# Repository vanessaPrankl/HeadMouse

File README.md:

# HeadMouse
 
This project provides hardware, enclosure and software for the head-motion based computermouse HeadMouse.

## Hardware
A BOM and PCB-files are provided in the hardware folder. A 600mAh LiPo-battery has been used for the prototyping, the battery only lasts for 3.5h in this case which is mainly caused by the high power consumption of the ESP32-S3-WROOM buetooth module. 

## Software
The following external libraries are utilized:
| Library | Provider | Licence |  
|------|----------|---------|
| [BleMouse](https://github.com/T-vK/ESP32-BLE-Mouse) | [T-vK](https://github.com/T-vK) | MIT License |
| [AdafruitBNO055](https://github.com/adafruit/Adafruit_BNO055) | [Adafruit](https://github.com/adafruit) | MIT License |
| [ESP32_TimerInterrupt](https://github.com/khoih-prog/ESP32TimerInterrupt) | [khoih-prog](https://github.com/khoih-prog) | MIT License|

Additionally, a HeadMouse library including major HeadMouse functions is provided. 

The hardware pins are configured in the hm_board_config_v1_0.hpp file of the headmouse library.
The default preferences are set in default_preferences.hpp (include folder of project).

## Enclosure
The enclosure consists of 2 3D-printed parts, 2 screws and according nuts for assembly and a sticky clip for mounting the deivce on the user's head.

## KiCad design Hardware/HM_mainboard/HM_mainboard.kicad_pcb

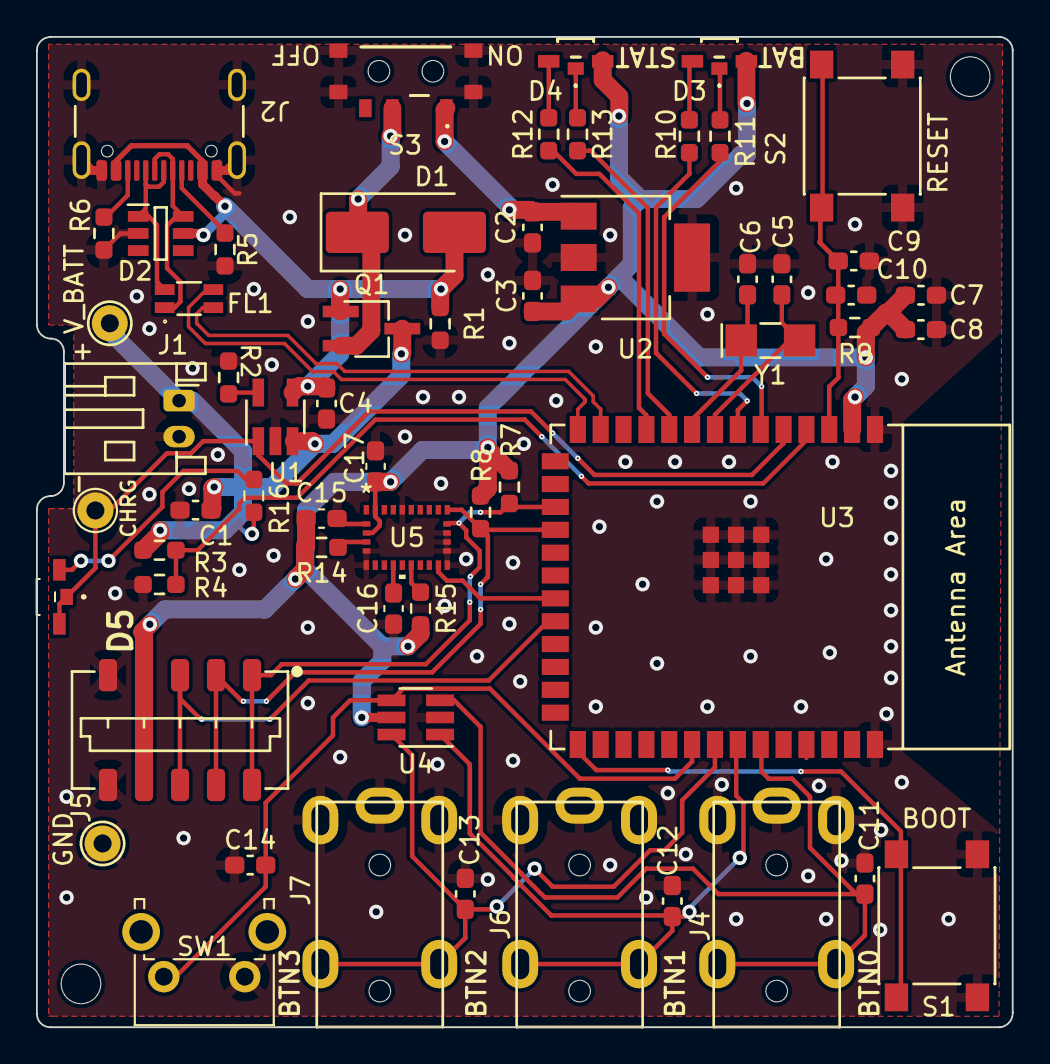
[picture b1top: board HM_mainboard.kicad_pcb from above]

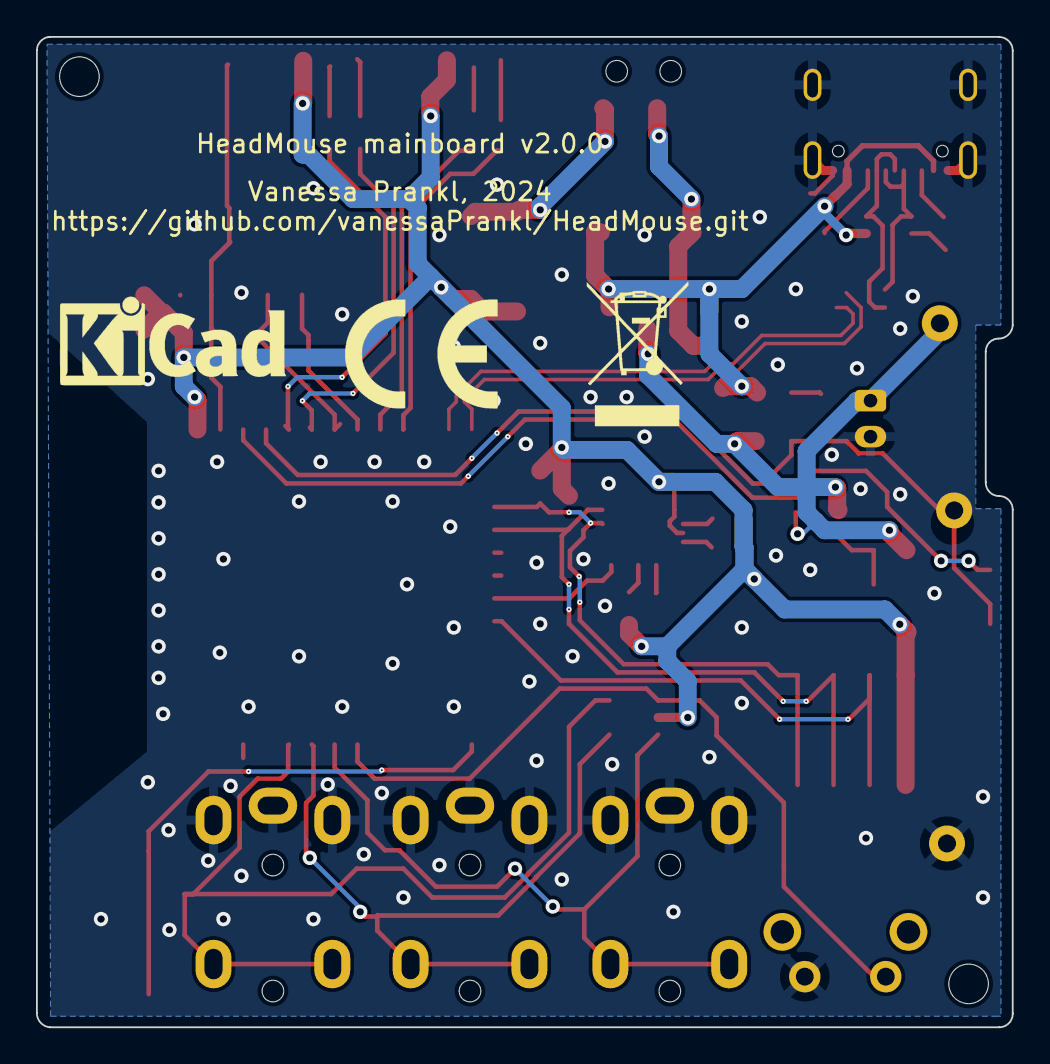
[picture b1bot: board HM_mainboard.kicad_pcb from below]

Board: 2 copper layers, 54.2 x 55.0 mm, 65 parts (3 on the bottom side), 39 nets.

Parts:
C1, C4: 4.7uF; C_0603_1608Metric_Pad1.08x0.95mm_HandSolder
C2, C3, C10, C16: 1.0uF; C_0603_1608Metric_Pad1.08x0.95mm_HandSolder
C5, C6: 15pF-1%; C_0603_1608Metric_Pad1.08x0.95mm_HandSolder
C7: 22uF; C_0603_1608Metric_Pad1.08x0.95mm_HandSolder
C8, C9, C11, C12, C13, C14, C15, C17: 100nF; C_0603_1608Metric_Pad1.08x0.95mm_HandSolder
D1: 10BQ015; D_SMB_Handsoldering
D2: WE-TVS-824015; SOT95P280X145-6N
D3, D4, D5: 155124RV73200
FL1: WE-CNSW 744232090; WE-CNSW-SMD
H1, H2: MountingHole; MountingHole_2.2mm_M2_ISO7380
J1: JST PH2P ST90; JST_PH_S2B-PH-K_1x02_P2.00mm_Horizontal
J2: USB4105-GF-A; USB_C_Receptacle_GCT_USB4105-xx-A_16P_TopMnt_Horizontal
J4, J6, J7: 54-00174
J5: 009159005551906
LOGO1: Logo_HM; LOGO_HM_V2.0.0
LOGO2: Logo_KiCAD; KiCad-Logo_5mm_SilkScreen
LOGO3: Logo_CE; CE-Logo_8.5x6mm_SilkScreen
LOGO4: Logo_WEEE; WEEE-Logo_5.6x8mm_SilkScreen
Q1: PMOS AS3401; TSOT-23_HandSoldering
R1, R9, R14, R15: 10k; R_0603_1608Metric_Pad0.98x0.95mm_HandSolder
R2: 2k; R_0603_1608Metric_Pad0.98x0.95mm_HandSolder
R3, R4: 100k; R_0603_1608Metric_Pad0.98x0.95mm_HandSolder
R5, R6: 5k1; R_0603_1608Metric_Pad0.98x0.95mm_HandSolder
R7: 4k7; R_0603_1608Metric_Pad0.98x0.95mm_HandSolder
R8: 1k8; R_0603_1608Metric_Pad0.98x0.95mm_HandSolder
R10, R11, R12, R13: 120; R_0603_1608Metric_Pad0.98x0.95mm_HandSolder
R16: 1k; R_0603_1608Metric_Pad0.98x0.95mm_HandSolder
S1, S2: SW_Push; SW_Push_1P1T_NO_6x6mm_H9.5mm
S3: 450404015514
SW1: SKHHLQA010; SW_Tactile_SPST_Angled_PTS645Vx58-2LFS
TP2, TP4, TP5: TestPoint_Probe; TestPoint_THTPad_D2.0mm_Drill1.0mm
U1: MCP73831-2; SOT-23-5_HandSoldering
U2: TC1262-33; SOT-223-3_TabPin2
U3: ESP32-S3-WROOM-1
U4: WE-TVS-824015043; SOT-23-6_Handsoldering
U5: BNO055; QFN_BNO055_BOS
Y1: 32.768 kHz; Crystal_SMD_MicroCrystal_CC7V-T1A-2Pin_3.2x1.5mm_HandSolder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

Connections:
3.3V: C3.1, C7.2, C8.2, C15.1, C17.1, D3.2 (A), D4.2 (A), J5.4, R7.2, R8.2, R9.2, R14.2, R15.2, U2.3 (VO), U3.2 (3V3), U4.5 (VBUS), U5.3 (VDD), U5.28 (VDDIO)
/BAT_CHRG_STATUS: D5.1 (K1), D5.3 (K2), TP4.1, U1.1 (STAT), U3.5 (GPIO5/TOUCH5/ADC1_CH4)
/BNO55_INT: U3.21 (GPIO13/TOUCH13/ADC2_CH2/FSPIQ/FSPIIO7/S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), U5.14 (INT)
/BTN_1: C11.1, J4.4, J4.5, U3.35 (MTMS/GPIO42), U4.3 (I/O2)
/BTN_2: C12.1, J6.4, J6.5, U3.34 (MTDI/GPIO41/CLK_OUT1), U4.1 (I/O1)
/BTN_3: C13.1, J7.4, J7.5, U3.33 (MTDO/GPIO40/CLK_OUT2), U4.6 (I/O4)
/BTN_4: C14.1, SW1.2, U3.32 (MTCK/GPIO39/CLK_OUT3/SUBSPICS1), U4.4 (I/O3)
/Battery_and_Power_Managment/V_IN: C2.1, S3.1, U2.1 (VI)
/Battery_and_Power_Managment/V_PWR_SWITCH: D1.1 (C), Q1.2 (S), S3.2
/I2C_SCL: J5.1, R7.1, U3.17 (GPIO9/TOUCH9/ADC1_CH8/FSPIHD/SUBSPIHD), U5.19 (COM1)
/I2C_SDA: J5.2, R8.1, U3.18 (GPIO10/TOUCH10/ADC1_CH9/FSPICS0/FSPIIO4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), U5.20 (COM0)
/LED_BAT_G: R10.1, U3.7 (GPIO7/TOUCH7/ADC1_CH6)
/LED_BAT_R: R11.1, U3.6 (GPIO6/TOUCH6/ADC1_CH5)
/LED_STAT_G: R12.1, U3.11 (GPIO18/U1RXD/ADC2_CH7/CLK_OUT3)
/LED_STAT_R: R13.1, U3.10 (GPIO17/U1TXD/ADC2_CH6)
/MPRLS_INT: J5.3, U3.22 (GPIO14/TOUCH14/ADC2_CH3/FSPIWP/FSPIDQS/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)
/Microcontroller - ESP32-S3-WROOM/BOOT: S1.2, U3.27 (GPIO0/BOOT)
/Microcontroller - ESP32-S3-WROOM/EN: C9.2, C10.2, R9.1, S2.2, U3.3 (EN)
/Microcontroller - ESP32-S3-WROOM/USB_C_D+: FL1.3, U3.14 (GPIO20/U1CTS/ADC2_CH9/CLK_OUT1/USB_D+)
/Microcontroller - ESP32-S3-WROOM/USB_C_D-: FL1.2, U3.13 (GPIO19/U1RTS/ADC2_CH8/CLK_OUT2/USB_D-)
/V_BAT_MEASURE: R3.1, R4.2, U3.4 (GPIO4/TOUCH4/ADC1_CH3)
GND: C1.2, C2.2, C3.2, C4.2, C5.1, C6.1, C7.1, C8.1, C9.1, C10.1, C11.2, C12.2, C13.2, C14.2, C15.2, C16.1, C17.2, D2.2 (GND), J1.2, J2.A1 (GND), J2.A12 (GND), J2.B1 (GND), J2.B12 (GND), J2.S1 (SHIELD), J4.1, J4.2, J4.3, J5.5, J6.1, J6.2, J6.3, J7.1, J7.2, J7.3, R1.1, R2.1, R4.1, R5.1, R6.1, S1.1, S2.1, S3.MP1, S3.MP2, S3.MP3, S3.MP4, SW1.1, TP5.1, U1.2 (V_{SS}), U2.2 (GND), U3.1 (GND), U3.40 (GND), U3.41 (GND), U4.2 (GND), U5.2 (GND), U5.5 (PS1), U5.6 (PS0), U5.15 (Pin15), U5.16 (Pin16), U5.17 (COM3), U5.18 (COM2), U5.25 (GNDIO)
unnamed: D2.1 (I/O), FL1.4, J2.A6 (D+), J2.B6 (D+)
unnamed: D2.6 (I/O), FL1.1, J2.A7 (D-), J2.B7 (D-)
unnamed: D3.1 (K1), R11.2
unnamed: D3.3 (K2), R10.2
unnamed: D4.1 (K1), R13.2
unnamed: D4.3 (K2), R12.2
unnamed: D5.2 (A), R16.1
unnamed: J2.A5 (CC1), R5.2
unnamed: J2.B5 (CC2), R6.2
unnamed: R2.2, U1.5 (PROG)
unnamed: C5.2, U3.8 (GPIO15/U0RTS/ADC2_CH4/XTAL_32K_P), Y1.2
unnamed: C6.2, U3.9 (GPIO16/U0CTS/ADC2_CH5/XTAL_32K_N), Y1.1
unnamed: C16.2, U5.9 (CAP)
unnamed: R14.1, U5.4 (NBOOT_LOAD_PIN)
unnamed: R15.1, U5.11 (NRESET)
V_BATT: C1.1, J1.1, Q1.3 (D), R3.2, R16.2, TP2.1, U1.3 (V_{BAT})
V_USB: C4.1, D1.2 (A), D2.5 (VDD), J2.A4 (VBUS), J2.A9 (VBUS), J2.B4 (VBUS), J2.B9 (VBUS), Q1.1 (G), R1.2, U1.4 (V_{DD})

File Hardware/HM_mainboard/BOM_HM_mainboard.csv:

"Reference","Value","Datasheet","Digikey","Mouser","Mouser Price/Stock","RS Components","Reichelt","Menge"
"AC1","LSM6DSOXTR","https://www.st.com/resource/en/datasheet/lsm6dsox.pdf","","LSM6DSOXTR","https://www.mouser.co.uk/ProductDetail/STMicroelectronics/LS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","","","1"
"C1, C4","4.7uF","~","","","","","","2"
"C2, C3, C10, C19","1.0uF-25V-(+80/-20%)","~","","F921E105KPA","","","","4"
"C5, C6","15pF-1%","~","","C0603C150F8HACAUTO","","","","2"
"C7","22uF","~","","","","","","1"
"C8, C9, C11-C18, C20","100nF","~","1276-CL10B104KB8NNNLCT-ND","581-06035C104K4","","200-6519","","11"
"D1","10BQ015","https://eu.mouser.com/ProductDetail/Vishay-Semiconductors/VS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","","10BQ015","https://eu.mouser.com/ProductDetail/Vishay-Semiconductors/VS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","","","1"
"D2","WE-TVS-824015","https://www.we-online.com/components/products/datasheet/824015.pdf","","824015","https://www.mouser.at/ProductDetail/Wurth-Elektronik/824015?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","","","1"
"D3, D4","155124RV73200","https://www.we-online.com/components/products/datasheet/1551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","","155124RV73200","https://www.mouser.at/ProductDetail/Wurth-Elektronik/155124R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","","","2"
"FL1","WE-CNSW 744232090","https://www.we-online.com/components/products/datasheet/7442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","","744232090","https://www.mouser.at/ProductDetail/Wurth-Elektronik/7442320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","","","1"
"J1","JST PH2P ST90 ","https://www.reichelt.at/at/de/jst-stiftleiste-90-1x2-polig-p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","","","https://www.reichelt.at/at/de/jst-stiftleiste-90-1x2-polig-p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","","JST PH2P ST90","1"
"J2","USB4105-GF-A","https://www.usb.org/sites/default/files/documents/usb_type-c.zip","","USB4105-GF-A","https://www.mouser.at/ProductDetail/GCT/USB4105-GF-A?qs=KUoI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","","","1"
"J3","Conn_01x04","~","","Beliebige Stiftleiste, Raster: 2.54mm","","","","1"
"J4-J7","54-00174","https://tensility.s3.amazonaws.com/uploads/pdffiles/54-00174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","54-00174","","https://www.digikey.de/de/products/detail/tensility-internat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","","","4"
"Q1","PMOS - AS3401","https://mm.digikey.com/Volume0/opasdata/d220001/medias/docus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","AS3401","","https://www.digikey.at/de/products/detail/anbon-semiconducto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","","","1"
"R1","10k/1%","","","RN73H1JTTD1002F100","https://www.mouser.at/ProductDetail/KOA-Speer/RN73H1JTTD1002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","","","1"
"R2","2k","","","ERJ-PA3J121V","","","","1"
"R3, R4, R7, R12-R14","10k","","","-- verschiedene Werte --","","","","6"
"R5, R6","5k1","","","RN73H1JTTD5101F100","https://www.mouser.at/ProductDetail/KOA-Speer/RN73H1JTTD5101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","","","2"
"R8-R11","120 ","","","ERJ-PA3J121V","","","","4"
"S1, S2","SW_Push","https://www.mouser.at/datasheet/2/358/typ_6x6_mm_tact_switch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","","13019315","https://www.mouser.at/ProductDetail/Schurter/1301.9315?qs=tG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","","","2"
"S3","450404015514","https://www.we-online.com/components/products/datasheet/4504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","","450404015514","https://www.mouser.co.uk/ProductDetail/Wurth-Elektronik/4504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","","","1"
"U1","MCP73831-2","http://ww1.microchip.com/downloads/en/DeviceDoc/20001984g.pdf","","MCP73831T-2ACI/OT","https://www.mouser.at/ProductDetail/Microchip-Technology/MCP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","","","1"
"U2","TC1262-33","http://ww1.microchip.com/downloads/en/DeviceDoc/21373C.pdf","","TC1262-3.3VDBTR","https://www.mouser.at/ProductDetail/Microchip-Technology/TC1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","","","1"
"U3","ESP32-S3-WROOM-1","https://www.espressif.com/sites/default/files/documentation/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","","ESP32-S3-WROOM-1-N8","https://www.mouser.at/ProductDetail/Espressif-Systems/ESP32-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","","","1"
"U4","WE-TVS-824015043","https://www.we-online.com/components/products/datasheet/8240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","","824015043","https://www.mouser.at/ProductDetail/Wurth-Elektronik/8240150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","","","1"
"U5","MC6470","https://www.mouser.at/datasheet/2/821/MC6470_Datasheet_APS_0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","","MC6470","https://www.mouser.at/ProductDetail/MEMSIC/MC6470?qs=u6%2FIM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","","","1"
"U6","BNO055","https://www.bosch-sensortec.com/media/boschsensortec/downloa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","828-1058","","https://www.digikey.at/en/products/detail/bosch-sensortec/BN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","","","1"
"Y1","32.768 kHz","https://www.mouser.at/datasheet/2/3/ABS07-3080027.pdf","","ASDK-32.768KHz-LRT","https://www.mouser.at/ProductDetail/ABRACON/ABS07-32768KHZ-T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","","","1"

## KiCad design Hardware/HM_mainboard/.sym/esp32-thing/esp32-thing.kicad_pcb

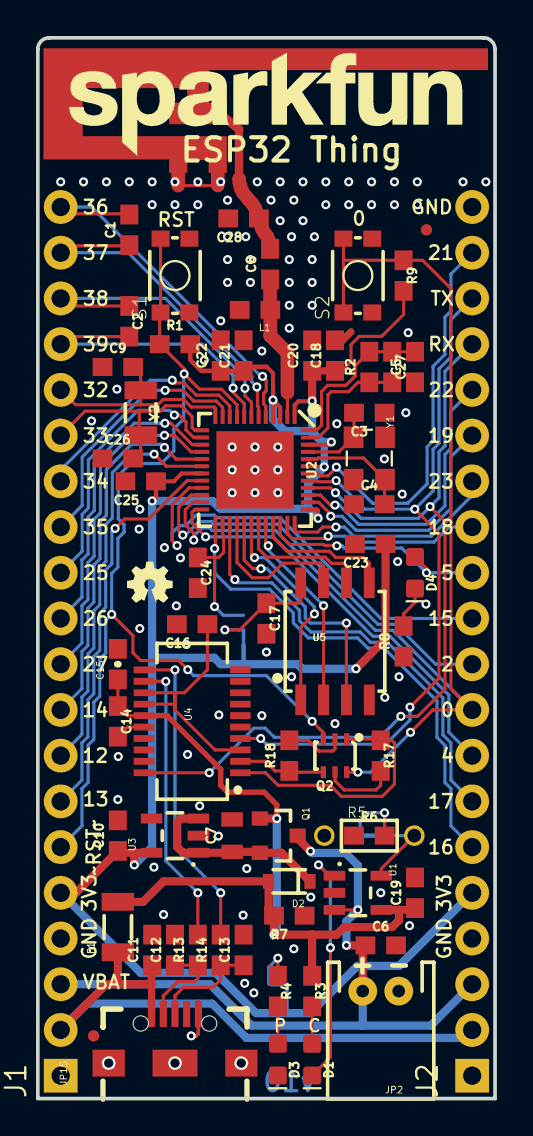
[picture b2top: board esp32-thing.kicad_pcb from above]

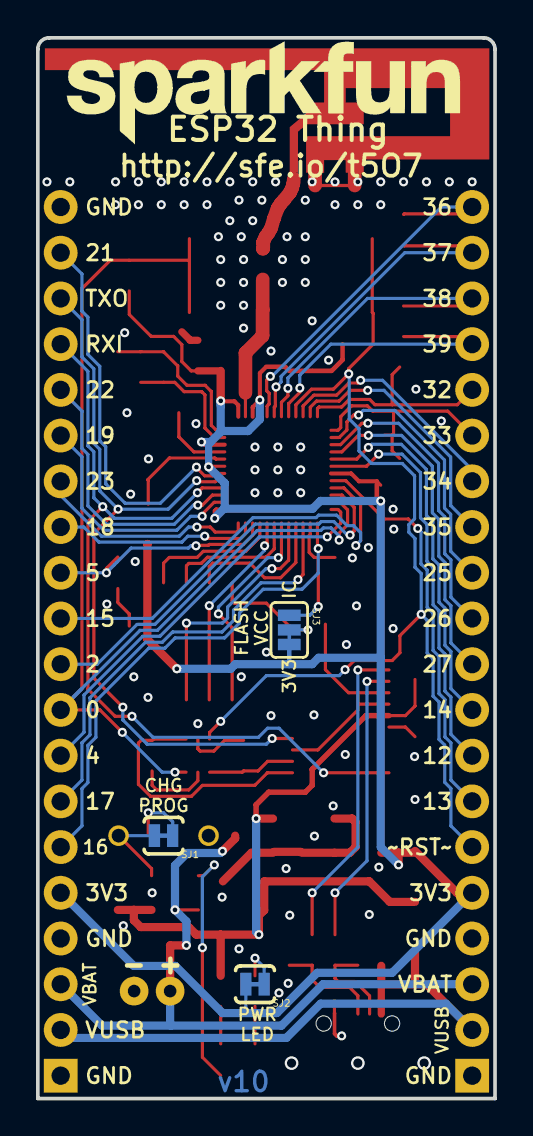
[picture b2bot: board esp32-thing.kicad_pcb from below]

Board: 2 copper layers, 25.4 x 58.9 mm, 72 parts (4 on the bottom side), 66 nets.

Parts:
C1, C2: 270pF; 0603
C3, C4: 10pF; 0603
C5: 10nF; 0603
C6, C19: 4.7uF; 0603
C7: 1.0uF; 0805
C8: 5.6pF; 0603
C9, C26: 15pF; 0603
C10: 2.2uF; 0603
C11, C14, C16, C17, C20, C21, C23, C25: 0.1uF; 0603
C12, C13: 47pF; 0603
C15: 4.7uF; 0603-CAP
C18: 100pF; 0603
C22: 10uF; 0603
C24: 1.0uF; 0603
C27: 3.0nF; 0603
C28: 2.4pF; 0603
D1: Yellow; LED-0603
D2: BAT20J; SOD-323
D3: RED; LED-0603
D4: BLUE; LED-0603
E1: ANTENNA; TRACE_ANTENNA_2.4GHZ_25.7MM_TUNED
F1: 500mA; PTC-1206
FD1, FD2: FIDUCIALUFIDUCIAL; MICRO-FIDUCIAL
FRAME1: FRAME-LEDGER; CREATIVE_COMMONS
J1, J2: 1X20_NOSILK
JP2: LiPo; JST-2-PTH
JP15: USB-B-MICRO-SMD_V03
L1: 2.7nH; 0603
LOGO1, LOGO3: SFE_LOGO_NAME.2_INCH; SFE_LOGO_NAME_.2
LOGO2: OSHW-LOGOMINI; OSHW-LOGO-MINI
Q1: 2.5A/30V; SOT23-3
Q2: MBT3904DW1T1; SC70-6
R1, R7, R9, R17, R18: 10k; 0603
R2: 20k; 0603
R3, R4: 1K; 0603
R5: DNP; 1_6W-RES
R6: 2.0k; 0603
R8: 330; 0603
R13, R14: 27; 0603
S1: RESET; TACTILE_SWITCH_SMD_4.6X2.8MM
S2: BTN-0; TACTILE_SWITCH_SMD_4.6X2.8MM
SJ1, SJ2: JUMPER-PAD-2-NC_BY_TRACE; PAD-JUMPER-2-NC_BY_TRACE_YES_SILK
SJ3: PAD-JUMPER-3-2OF3_NC_BY_TRACE_YES_SILK_FULL_BOX
U1: MCP73831; SOT23-5
U2: ESP3212; QFN48-0.4MM
U3: AP2112K-3.3V; SOT23-5
U4: FT231XS; SSOP20_L
U5: W25Q32FVSS; SOIC-8
Y1: 26MHz; CRYSTAL-SMD-3.2X2.5
Y2: 32.768kHz; CRYSTAL-SMD-3.2X1.5MM

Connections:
0: J2.9, Q2.6, R9.1, S2.3, S2.4, U2.23
2: J2.10, U2.22
3.3V: C10.1, C18.1, C20.1, C21.1, C22.1, C23.1, C25.1, J1.5, J2.5, R1.2, R9.2, SJ2.2, SJ3.3, U2.1, U2.3, U2.4, U2.19, U2.37, U2.43, U2.46, U3.5
3.3V_F: C16.1, U4.3, U4.13, U4.14
4: J2.8, U2.24
5: D4.A, J2.12, U2.34
12: J1.8, U2.18
13: J1.7, U2.20
14: J1.9, U2.17
15: J2.11, U2.21
16: J2.6, U2.25
17: J2.7, U2.27
18: J2.13, U2.35
19: J2.15, U2.38
21: J2.19, U2.42
22: J2.16, U2.39
23: J2.14, U2.36
25: J1.12, U2.14
26: J1.11, U2.15
27: J1.10, U2.16
32K_XN: C26.2, J1.15, U2.13, Y2.P$2
32K_XP: C9.2, J1.16, U2.12, Y2.P$1
34: J1.14, U2.10
35: J1.13, U2.11
36: C1.2, J1.20, U2.5
37: C1.1, J1.19, U2.6
38: C2.1, J1.18, U2.7
39: C2.2, J1.17, U2.8
CAP_10N: C5.2, C27.1, R2.2, U2.48
CHIP_PU: J1.6, Q2.3, R1.1, S1.3, S1.4, U2.9
D+: C13.1, JP15.D+, R14.1
D-: C12.1, JP15.D-, R13.1
DTR: Q2.1, R17.1, U4.1
FLASH_SCK: U2.31, U5.6
FLASH_SCS: U2.30, U5.1
FLASH_SDI: U2.33, U5.5
FLASH_SDO: U2.32, U5.2
FLASH_SHD: U2.28, U5.7
FLASH_SWP: U2.29, U5.3
FLASH_VDD: C24.1, SJ3.1, U2.26
GND: C3.1, C4.1, C5.1, C6.2, C7.2, C9.1, C10.2, C11.2, C12.2, C13.2, C14.2, C15.2, C16.2, C17.2, C18.2, C19.2, C20.2, C21.2, C22.2, C23.2, C24.2, C25.2, C26.1, C28.2, D3.C, E1.GND, E1.GND2, J1.1, J1.4, J2.1, J2.4, J2.20, JP2.1, JP15.GND, L1.2, R5.1, R6.1, R7.1, R8.1, S1.1, S1.2, S2.1, S2.2, U1.2, U2.EP, U3.2, U4.6, U4.16, U5.4, Y1.2, Y1.4
LNA_IN: C8.1, L1.1, U2.2
unnamed: D4.C, R8.2
unnamed: D3.A, R4.2
unnamed: R4.1, SJ2.1
unnamed: C27.2, R2.1, U2.47
unnamed: R13.2, U4.12
unnamed: R14.2, U4.11
unnamed: D1.C, U1.1
unnamed: Q2.5, R17.2
unnamed: C17.1, SJ3.2, U5.8
unnamed: Q2.2, R18.2
unnamed: C3.2, U2.45, Y1.1
unnamed: R5.2, SJ1.2, U1.5
unnamed: C4.2, U2.44, Y1.3
unnamed: R6.2, SJ1.1
unnamed: D1.A, R3.2
RTS: Q2.4, R18.1, U4.2
SHIELD: JP15.SHIELD1, JP15.SHIELD2, JP15.SHIELD3
TRACE_ANT: C8.2, C28.1, E1.ANT
U0RXD: J2.17, U2.40, U4.20
U0TXD: J2.18, U2.41, U4.4
VIN: C7.1, D2.C, Q1.2, U3.1, U3.3
VUSB-RAW: C11.1, F1.1, J1.2, J2.2, JP15.VBUS
V_BATT: C6.1, J1.3, J2.3, JP2.2, Q1.3, U1.3
V_USB: C14.1, C15.1, C19.1, D2.A, F1.2, Q1.1, R3.1, R7.2, U1.4, U4.15

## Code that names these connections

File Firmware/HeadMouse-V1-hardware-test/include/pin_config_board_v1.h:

/* CIRCUIT BOARD V1 PIN CONFIG *********************************************/
/* 
/* Description: This is a hardware pin config file for HeadMouse board version 1.
/* Author: Vanessa Prankl
/* Date: 26.03.2024
/* 
/************************************************************************/
#pragma once
#include <Arduino.h>

/* LEDs */
const int8_t PIN_LED_BAT_R = 6;
const int8_t PIN_LED_BAT_G = 7;
const int8_t PIN_LED_STATUS_R = 17;
const int8_t PIN_LED_STATUS_G = 18;

/* Buttons */
const int8_t PIN_BTN_1 = 42;
const int8_t PIN_BTN_2 = 41;
const int8_t PIN_BTN_3 = 40;
const int8_t PIN_BTN_4 = 39;

/* Battery */
const int8_t PIN_VBATT_MEASURE = 4;     /* Current battery voltage */
const int8_t PIN_BATT_STATUS = 5;       /* Pulled low if charging is active*/

/* I2C */
const int8_t PIN_I2C_SCL = 9;
const int8_t PIN_I2C_SDA = 10;

/* IMU interrupt pins */
const int8_t PIN_LSM6DS_INT = 11;
const int8_t PIN_MC6470_INT = 12;
const int8_t PIN_BNO55_INT = 13;

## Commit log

2023-11-20 First Schematic for Headmouse
2023-11-20 Updated Comment
2023-11-20 Added PDF Schematic
2023-11-26 Create .gitignore
    added .gitignore
2023-11-27 General schematic improvements
    - Replaced ESP32-WROOM by ESP32-S3-WROOM
    - Removed autonomous reboot option (not needed for ESP32-S3)
    - Added clock crystal footprint
    - Replaced USB-C version 3 with USB- v2 due to less connections
    - Added TVS-array to USB-C connector
    - Added inductance to USB-C connector for noise reduction
2023-11-27 Added TVS-Diodes for button jacks
2023-11-27 Updated components of power supply unit
    - Replaced PMOSFET
    - Replaced LDO
    - Replaced battery charger
    - Replaced caps and resistors
    - Replaced battery connector
2023-11-27 Moved old versions to archive folder
2023-11-27 Added new pdf shematic report
2023-11-28 Updated port connectors to new microcontroller
2023-11-28 Updated port connectors of microcontroller
2023-12-02 Added IMUs, updated some components
    - Added 2 additonal IMUs:
    1) 6-Axis MC6470
    2) 9-Axis BNO55
    - Replaced button jack connectors
    - Replaced battery charging LED by a charging status measurement circuit
    - Replaced caps for clock crystal
2023-12-03 Changed I2C address selection of IMUs
2023-12-03 Added pull-ups to i2c connections
2023-12-03 Started component placement for PCB
2023-12-05 Updated footprint of auxiliary jacks, routed first version of PCB
2023-12-05 Added gerber and drill files
2023-12-06 Added BOM
2023-12-06 Removed temp. file
2023-12-11 Moved measurement lines. Updated PCB according to Aisler DRC
2023-12-11 Updated BOM
2023-12-13 Removed autosaved schematic
2024-01-18 Added hardware test firmware for board V1
2024-01-18 Added project documentation and master thesis draft
2024-02-05 Replaced Arduino hardware test by platform io project
2024-02-06 Added test program for IMUs
    * Added IMU data sheets
    * Added test program for IMUs (not working yet)
2024-02-06 Finished LSM6DSO IMU test - everything working
2024-02-06 Added BNO055 library
2024-03-17 Fixed wrong symbol-to-footprint assignment of PMOS AS3401
2024-03-17 Swapped battery polarity due to wrong pinning assumption
    Bugfix
2024-03-17 Fixed missing GND connections of BNO055 at Pin 15 and 16
    Bugfix due to wrong pin assignments in symbol library
2024-03-17 Added testpoints to pcb
2024-03-17 Added gerber files and schematic printed to pdf
2024-03-26 Added MC6470 library and hardware test
    Accelerotemeter works as intended, magnetometer seems to be only a dummy function not really measuring anything.
2024-03-28 Added basic HAL for magnetormeter measurements of MC6470
    Not tested yet
2024-03-28 Update magnetometer init function
2024-03-28 Finished Magnetometer HAL. Tested and runningn now
2024-03-28 Fixed temperature measurement issue
2024-03-28 Improved pcb layout design
2024-04-04 Added lib and test probram for BLE mouse control. Tested and working
2024-04-08 Moved a wire
2024-04-08 Updated thesis documentation
2024-04-08 Added test program for simple conversion between imu rotation and mouse cursor movement. Works well
2024-04-11 Added connector for sip&puff sensor
2024-04-11 Added BOM for V1.1.0
2024-04-11 Added hardware version to PCB silkscreen
2024-04-17 Updated schematic and PCB according to Email from BA on 16th of April
2024-04-18 Uniform text alignment
2024-04-18 Added BOM for updated PCB-design; Added PDF-schematic
2024-04-18 Removed Documentation folder due to merge issues
2024-04-29 Added test example for mouse control by accelerometer
2024-05-09 Splitted IMU mouse test into relative and absolute mode
2024-05-13 Finished test program for relative mouse mode
    Program needs further improvement to make it faster
2024-05-13 Added relative mode with LSM6DSO IMU addtionally to MCP6470 IMU
2024-05-15 Updated peripheral test program to calculate correct voltage from battery voltage measurement
2024-05-16 Updated peripheral test program to indicate battery charging status by led
2024-05-16 Added test documentation for pcb V1.1.1
2024-05-21 Added test program for bno055 IMU. Not finished yet
2024-05-27 Added second test program for bno055 with another library, as the first one does not seem to work.
2024-05-28 Got BNO055 test running
2024-06-07 Heureka, BNO is up and running! ~\o.O/~
2024-06-20 Finished absolute mouse Test. Up and running smoothly
2024-06-20 Added VSCode project for headmouse firmware implementation based on hardware test project
2024-06-24 Added basic firmware architecture for headmouse
2024-06-27 Added code descriptions
2024-06-27 Added serial comm config
2024-06-27 Added missing code to logging file
2024-06-27 Updated basic headmouse methods and attributes
2024-06-27 Added log level for battery logging
2024-06-27 Added error type for out of range error of variables
2024-06-27 Moved headmouse header file
2024-06-27 Added error squiggles to vs code project
2024-06-27 Added default preferences for device config
2024-06-27 Added some major HeadMouse functions
    * device init
    * set preferences
    * get current BLE connection status
    * get current charging status
2024-06-27 Added setup for headmouse firmware
2024-06-27 Fixed wrong syntax of enum
2024-06-27 Added log prefix for IMU debugging
2024-06-27 Added IMU calibration check
2024-06-27 Added some log messages and IMU calibration check
2024-07-02 Added battery voltage levels for status description
2024-07-02 Added compile commands for sonar linter
2024-07-02 Added battery measurement and status description
2024-07-02 Corrected spelling mistake
2024-07-02 Reorganized headmouse methods
2024-07-02 Added led types
2024-07-02 Added sensitivity levels. need to be tested
2024-07-02 Reorganzed headmouse methods
2024-07-02 Reorganized main
2024-07-04 Finished battery status interpreter
2024-07-04 Finished device status interpreter
2024-07-04 Added error message to i2c bus init
2024-07-04 Removed unused error var
2024-07-04 Added log messages; moved updateDevStatus method
2024-07-04 Minor corrections
2024-07-09 Updated logging lib
2024-07-09 Moced borad config file
2024-07-09 Updated error enum
2024-07-09 Removed minor syntax mistakes
2024-07-09 Finished basic device status test.
2024-07-09 Updated log messages at init and debudged led state control
2024-07-14 Finished hardware timer- & pin change interrupt test
2024-07-14 Interrupt test is now able to differentiate between two buttons instead of only one
2024-07-14 Updated program description of interrupt test program
2024-07-14 Added lib for button click/press detection based on hardware isr
2024-07-16 Adopted setButtonActions of HeadMouse class to new button class
2024-07-16 Added button click/press evaluation
2024-07-16 Removed error code from setPreferences function of HeadMouse and removed not necassary include
2024-07-16 Added button click status reset
2024-07-17 Added LED implementation. Reorganized def files
2024-07-21 finalized hw timer implementation of LEDs. Removed multiple definiton linker error
2024-07-23 Updated function descriptions
2024-07-23 Fixed bug in button action preferences settings
2024-07-24 fixed bug in movement detection. Basically working now, minor improvements in movement detection required
2024-07-28 Some code optimizations
2024-07-29 Updated schematic to version v2.0.0
    • Removed two 6-Axis IMUs
    • As the BNO055 did not respond to I2C requests, a 2k7 pullup was added in parallel to the I2C-SDA pullup. The behavior is described here: https://forums.adafruit.com/viewtopic.php?t=205215
    • Added mounting holes for enclosure
    • Added board description prints
2024-07-30 Added BOM, PDF and zipped V2.0.0 project data
2024-07-30 Removed documentation folder due to reoccuring merge issues
2024-07-30 Removed documentation folder due to reocurring merge issues
2024-08-01 Update ble connection mechanism. Multiple device can now be connected and auto reconnect was implemented
2024-08-01 Added autonomous reconnection when connection is interrupted/lost.
2024-08-04 Finished Bluetooth implementation. BLE repairs automatically and pairing can be invoked via button. No differentiation between manual pairing and connection lost pairing (device pairs to the next ava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
2024-08-06 Improved mouse accuracy by storing data when offset cutoff for mouse stabalization occurs
2024-08-08 Added hysteresis for battery level detection to prevent jitter when transitioning from one level to the other
2024-08-11 created 3D assembly of pcb board
2024-08-11 Clean up kicad
2024-08-12 Created bottom case
2024-08-12 Replaced weak pullup at battery charging status by 1k pullup
2024-08-19 updated schematic
2024-08-19 Finished bottom case design
2024-08-19 Copied bottm case design as starting point for top case design
2024-08-21 Finished first version of enclosure including 3D-print files
2024-08-21 Improved enclosure print quality
2024-08-21 finished Enclosure for HeadMouse PCB V2
2024-08-23 Added connector for sip&puff sensor to enclosure
2024-08-26 Added firmware test for non static memory access
2024-08-26 Revert "Added firmware test for non static memory access"
    This reverts commit 5fe53a0665920e0c76a471c3cd0a6c3daba7b6d1.
2024-08-26 Added firmware test for usage of non volatile memory on ESP
2024-08-28 Fixed most annoying Fault in the whole project. Caused my buttons to behave like vodoo. FML!!!
    for(int i=0; i++; i<max)
    is NOT the same as
    for(int i=0; i<max; i++)
    Life sucks, this occured 3 times in my program and idk why because i did not test the feature for 2 weeks and it worked before. Anyway, fixed now.
2024-08-31 Fixed wrong alignment issue in for-loop of LED library
2024-08-31 Added speed dependant sensitivtiy-ramp-up for detailed positioning of the mouse cursor and de-jitter
2024-09-04 Optimized sensitivity rampup and jitter
2024-10-14 Removed unnecessary imu libraray
2024-10-14 Added program cycle timer for power saving

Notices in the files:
parts and their libraries:
https://creativecommons.org/licenses/by-sa/4.0
Released under the Creative Commons Attribution Share-Alike 4.0 License
